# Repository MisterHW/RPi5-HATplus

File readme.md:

# Raspberry Pi HAT+ Template

With the relase of the Raspberry Pi 5, a new HAT form factor (HAT+) was introduced. It has cutouts for both a PCIe and two 4-lane CSI-2 camera ports.

## Template Project

Minimum KiCAD version: 7.0.10

Bottom-entry 2x20, 2.54mm SMD socket header: 
- [Samtec HLE-120-02-L-DV-BE-A-K-TR](https://www.samtec.com/products/hle-120-02-l-dv-be-a-k-tr)
- [WE 610040243021](https://www.we-online.com/en/components/products/PHD_2_54_SMT_DUAL_SOCKET_HEADER_BOTTOM_ENTRY_6100XX243021)

Extender 2x20, 2.54mm socket header: 
- [Samtec ESQ-120-14-G-D](https://www.samtec.com/standards/pc104/pc104)
- [Sparkfun PRT-16764](https://www.mouser.com/ProductDetail/SparkFun/PRT-16764?qs=W%2FMpXkg%252BdQ4FKwyaXnhaEw%3D%3D)

## Links

HAT+ spec: https://datasheets.raspberrypi.com/hat/hat-plus-specification.pdf

RPi5 mechanical drawing: https://datasheets.raspberrypi.com/rpi5/raspberry-pi-5-mechanical-drawing.pdf

HAT+ EEPROM: https://github.com/raspberrypi/utils/tree/master/eeptools

PCIe: https://datasheets.raspberrypi.com/pcie/pcie-connector-standard.pdf   
(inofficial early work: https://github.com/m1geo/Pi5_PCIe)

## Mechanical Specification

### Dimensions

Board outline:

Flexprint connector locations (with some dimensions added):

The exact center positions of the flex cables leaving the RPi5 board are needed to avoid vertical offset between connector pairs.

While mostly cosmetic for long cables which can accommodate such offsets by twisting, short cables (<= 60 mm) may end up inserted askew.

### Pinout

#### GPIO

(source: [raspberrypi.com](https://www.raspberrypi.com/documentation/computers/raspberry-pi.html))

#### CSI-2

Differential pairs are on the Pin-1 side and easily identified in context (22-pin to 15-pin flexprint adapter):

(adapted from: [thepihut](https://thepihut.com/blogs/raspberry-pi-tutorials/how-to-use-two-camera-modules-with-raspberry-pi-5))

J3, J4 markings: Pin-22 side.

Right-side contacts.

#### PCIe

Based on the image by [M1GEO] and subsequent official specification:

J20 marking: Pin-1 side.

Right-side contacts.

### Board Positions

The alignments of PCIe and CSI-2 connectors are given in the User.Drawings layer.

## License

KiCad project: copyright Helge Wurst 2024.

This source describes Open Hardware and is licensed under the CERN-OHL-S v2.

You may redistribute and modify this source and make products using it under the terms of the CERN-OHL-S v2 (https://ohwr.org/cern_ohl_s_v2.txt).

This source is distributed WITHOUT ANY EXPRESS OR IMPLIED WARRANTY, INCLUDING OF MERCHANTABILITY, SATISFACTORY QUALITY AND FITNESS FOR A PARTICULAR PURPOSE. Please see the CERN-OHL-S v2 for applicable conditions.

Source location: https://github.com/MisterHW/RPi5-HATplus

As per CERN-OHL-S v2 section 4, should You produce hardware based on this source, You must where practicable maintain the Source Location visible on the external case of the Gizmo or other products you make using this source.

## Changes

- 2024-03 initial release.

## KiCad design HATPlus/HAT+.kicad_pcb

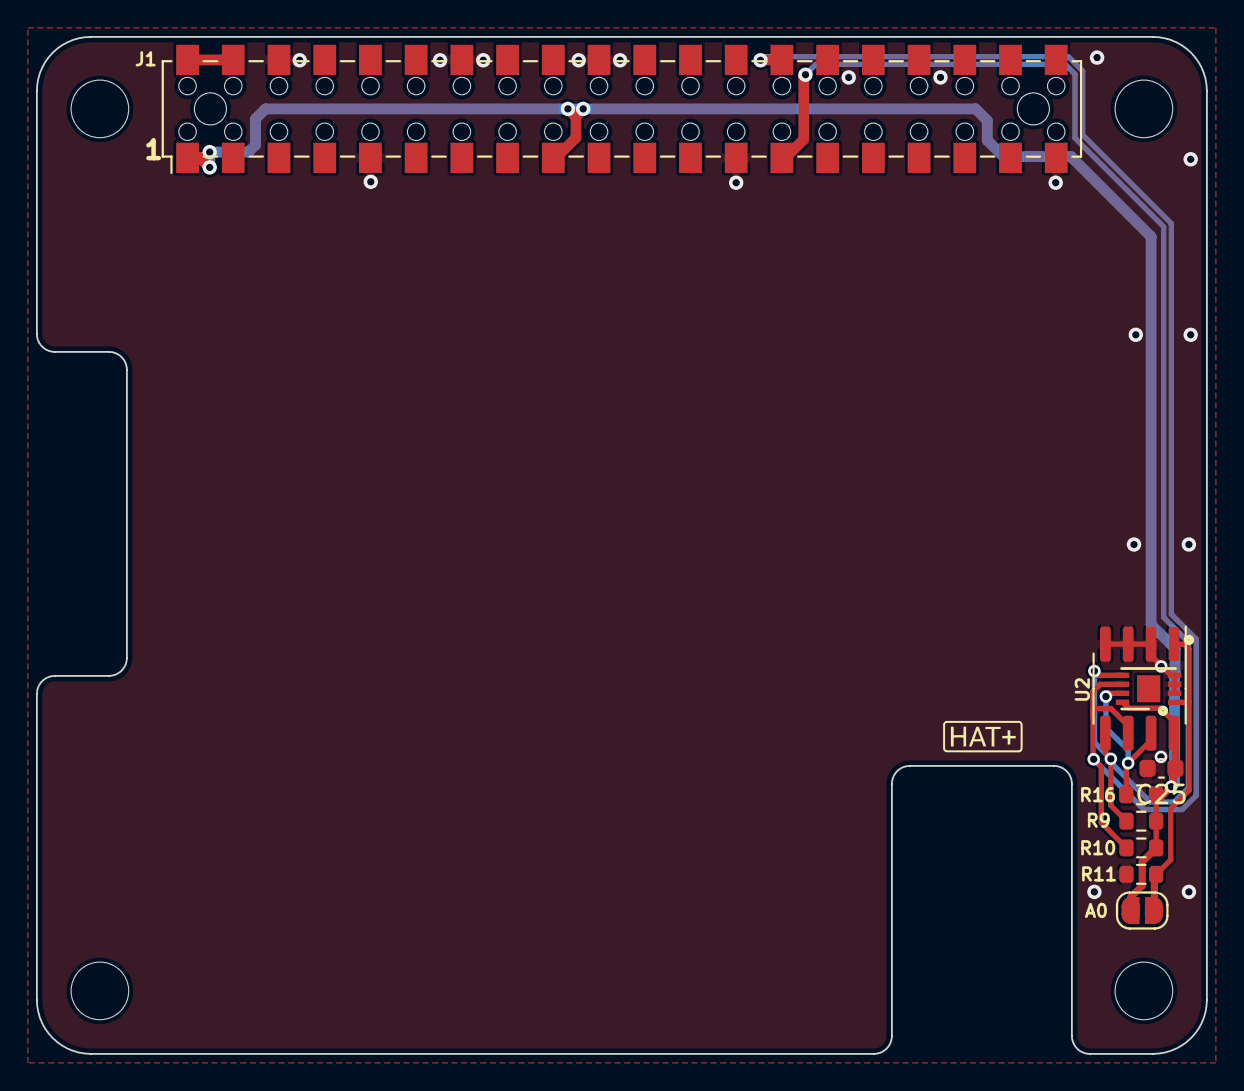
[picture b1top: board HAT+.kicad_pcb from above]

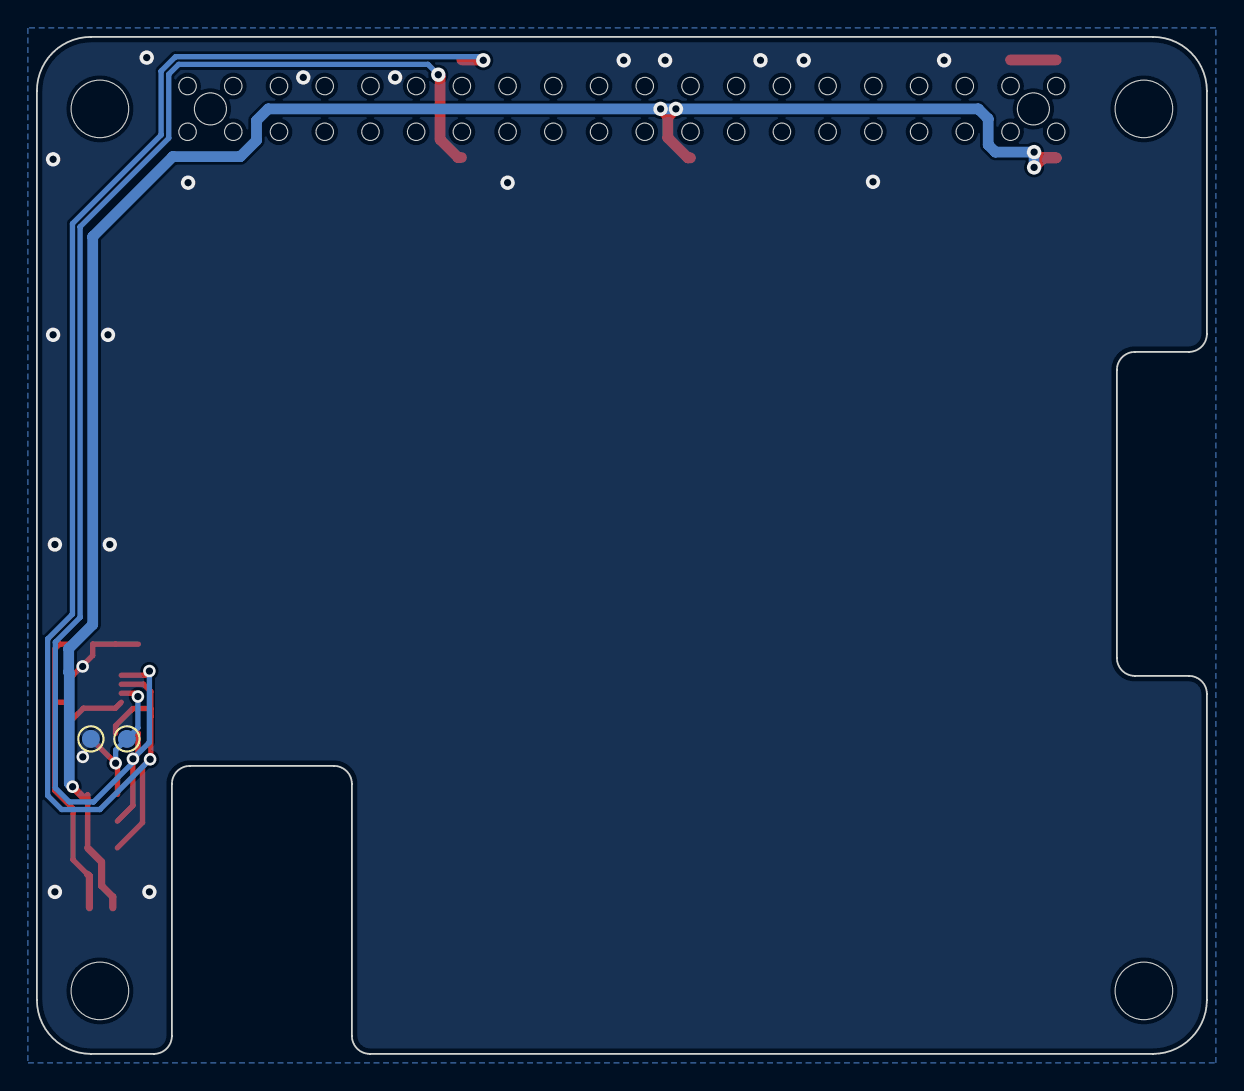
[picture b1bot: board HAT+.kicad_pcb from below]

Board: 4 copper layers, 65.0 x 56.5 mm, 15 parts (2 on the bottom side), 7 nets.

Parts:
A0: SolderJumper_2_Open; SolderJumper-2_P1.3mm_Open_RoundedPad1.0x1.5mm
C25: 100nF; C_0603_1608Metric
GND1: TestPoint_Alt; TestPoint_Pad_D1.0mm
H1, H2, H3, H4: MountingHole 3.2mm; MountingHole_3.2mm_M3_DIN965
J1: Conn_02x20_Odd_Even; Samtec_HLE-120-02-xxx-DV-BE-A_2x20_P2.54mm_Horizontal_Rever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
R9, R10, R11, R16: 3.9k; R_0603_1608Metric
U1: AT24CS64-SSHM; SOIC-8_3.9x4.9mm_P1.27mm
U2: AT24CS64-MAHM; DFN-8-1EP_3x2mm_P0.5mm_EP1.3x1.5mm
WP1: TestPoint_Alt; TestPoint_Pad_D1.0mm

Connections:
/HAT+/HAT_3V3: A0.2 (B), C25.1, J1.1, J1.17, R9.2, R10.2, R16.2, U1.8 (VCC), U2.8 (VCC)
/HAT+/HAT_5V0: J1.2, J1.4
/HAT+/HAT_SCL0: J1.28, R10.1, U1.6 (SCL), U2.6 (SCL)
/HAT+/HAT_SDA0: J1.27, R9.1, U1.5 (SDA), U2.5 (SDA)
GND: C25.2, GND1.1, J1.6, J1.9, J1.14, J1.20, J1.25, J1.30, J1.34, J1.39, R11.1, U1.2 (A1), U1.3 (A2), U1.4 (GND), U2.2 (A1), U2.3 (A2), U2.4 (GND)
unnamed: A0.1 (A), R11.2, U1.1 (A0), U2.1 (A0)
unnamed: R16.1, U1.7 (WP), U2.7 (WP), WP1.1
